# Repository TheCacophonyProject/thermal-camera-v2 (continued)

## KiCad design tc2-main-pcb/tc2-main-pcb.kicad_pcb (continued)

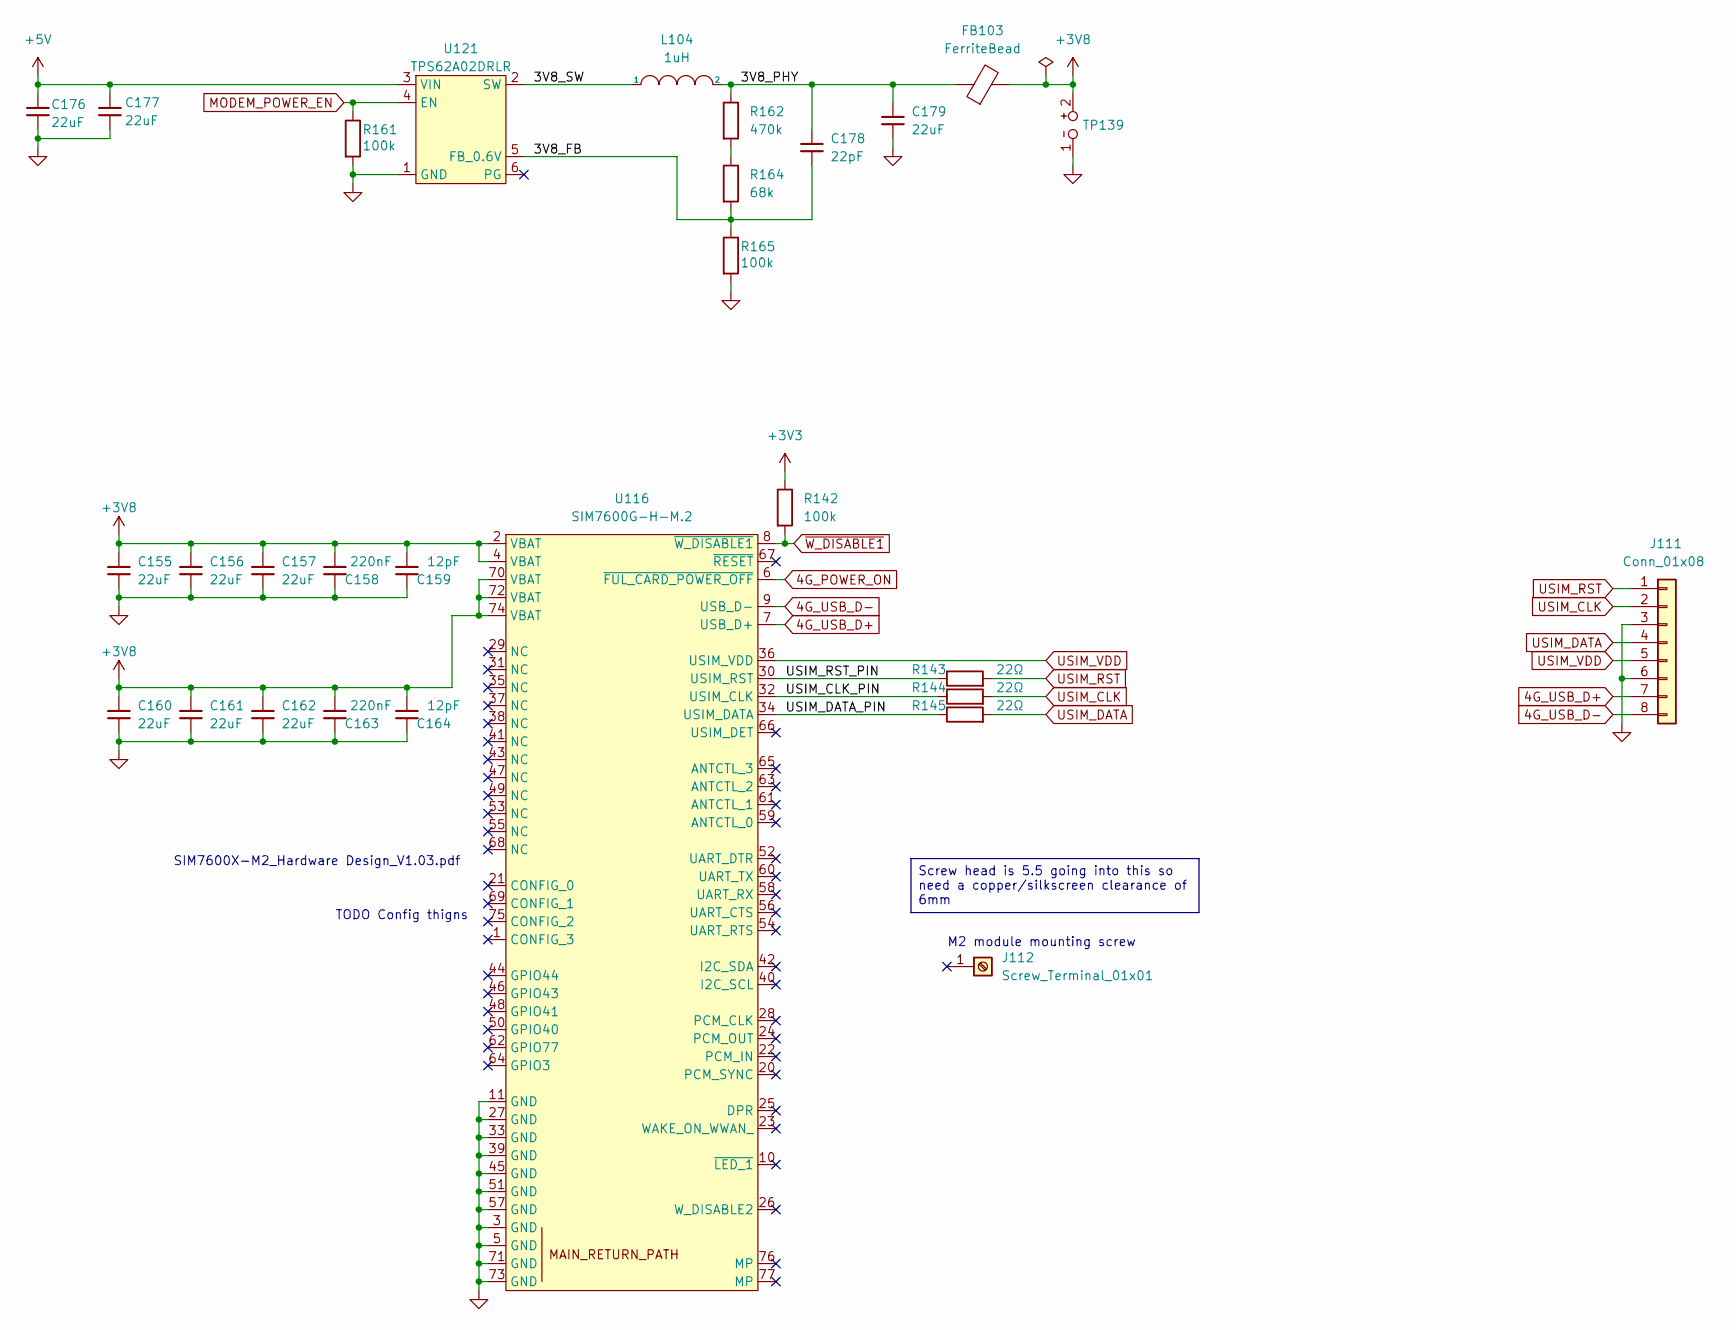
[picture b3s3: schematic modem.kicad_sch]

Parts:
C155, C156, C157, C160, C161, C162, C176, C177, C179: 22uF; C_0603_1608Metric; LCSC Part C86295
C158, C163: 220nF; C_0402_1005Metric; LCSC Part C16772
C159, C164: 12pF; C_0402_1005Metric; LCSC Part C1547
C178: 22pF; C_0402_1005Metric; LCSC Part C1555
FB103: FerriteBead; L_0805_2012Metric; LCSC Part C76818
J111: Conn_01x08; sim-usb-pcb
J112: Screw_Terminal_01x01; M2_modem_mount_screw; LCSC Part C2928176
L104: 1uH; L_1008_2520Metric; LCSC Part C285917
R142, R161, R165: 100k; R_0402_1005Metric; LCSC Part C25741
R143, R144, R145: 22Ω; R_0402_1005Metric; LCSC Part C25092
R162: 470k; R_0402_1005Metric; LCSC Part C319591
R164: 68k; R_0402_1005Metric; LCSC Part C445618
TP139: TP_2P; test-point-2p
U116: SIM7600G-H-M.2; M.2; LCSC Part C2761526
U121: TPS62A02DRLR; SOT-563; LCSC Part C5350187

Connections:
4G_POWER_ON: U116.6 (~FUL_CARD_POWER_OFF); also elsewhere on the board
4G_USB_D+: J111.7, U116.7 (USB_D+)
4G_USB_D-: J111.8, U116.9 (USB_D-)
+3V3: R142.1; also elsewhere on the board
+3V8: C155.1, C156.1, C157.1, C158.2, C159.2, C160.1, C161.1, C162.1, C163.2, C164.2, FB103.2, TP139.2, U116.2 (VBAT), U116.4 (VBAT), U116.70 (VBAT), U116.72 (VBAT), U116.74 (VBAT)
+5V: C176.1, C177.1, U121.3 (VIN); also elsewhere on the board
/modem/3V8_FB: C178.2, R164.2, R165.1, U121.5 (FB_0.6V)
/modem/3V8_PHY: C178.1, C179.1, FB103.1, L104.2, R162.1
/modem/3V8_SW: L104.1, U121.2 (SW)
/modem/USIM_CLK_PIN: R144.1, U116.32 (USIM_CLK)
/modem/USIM_DATA_PIN: R145.1, U116.34 (USIM_DATA)
/modem/USIM_RST_PIN: R143.1, U116.30 (USIM_RST)
GND: C155.2, C156.2, C157.2, C158.1, C159.1, C160.2, C161.2, C162.2, C163.1, C164.1, C176.2, C177.2, C179.2, J111.3, J111.6, R161.2, R165.2, TP139.1, U116.3 (GND), U116.5 (GND), U116.11 (GND), U116.27 (GND), U116.33 (GND), U116.39 (GND), U116.45 (GND), U116.51 (GND), U116.57 (GND), U116.71 (GND), U116.73 (GND), U121.1 (GND); also elsewhere on the board
MODEM_POWER_EN: R161.1, U121.4 (EN); also elsewhere on the board
unnamed: R162.2, R164.1
USIM_CLK: J111.2, R144.2
USIM_DATA: J111.4, R145.2
USIM_RST: J111.1, R143.2
USIM_VDD: J111.5, U116.36 (USIM_VDD)
~W_DISABLE1: R142.2, U116.8 (~W_DISABLE1); also elsewhere on the board

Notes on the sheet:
TODO Config thigns
M2 module mounting screw
SIM7600X-M2_Hardware Design_V1.03.pdf
Screw head is 5.5 going into this so need a copper/silkscreen clearance of 6mm

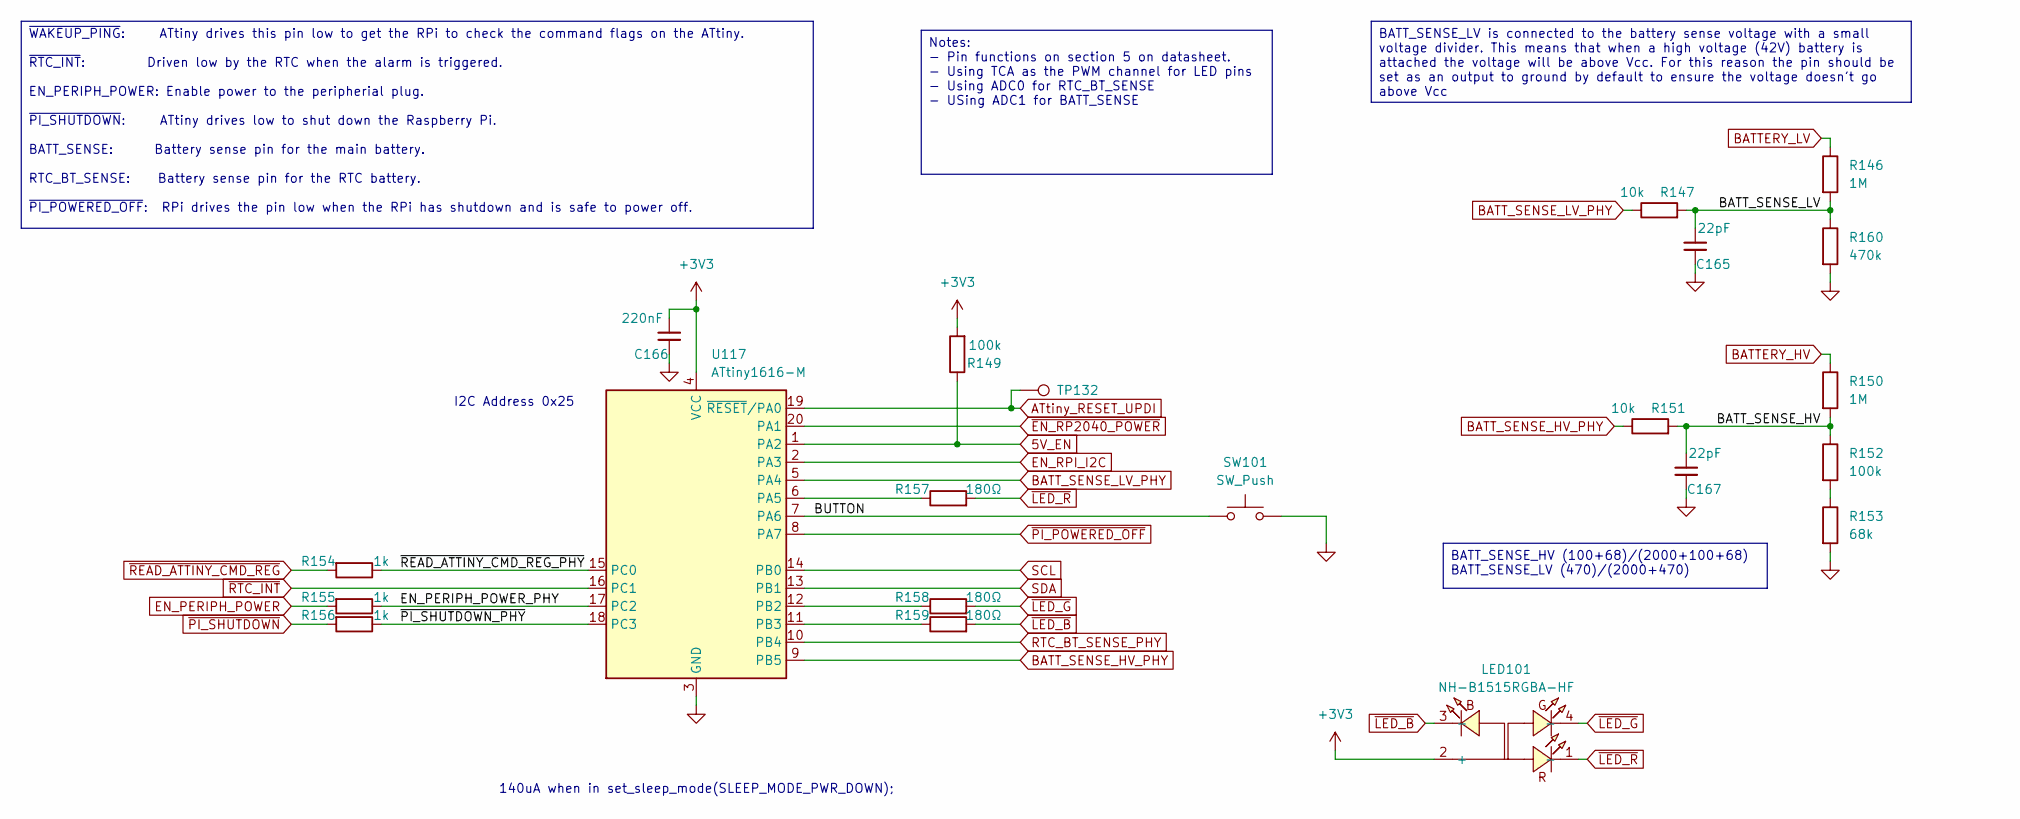
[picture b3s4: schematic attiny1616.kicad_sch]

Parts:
C165, C167: 22pF; C_0402_1005Metric; LCSC Part C1555
C166: 220nF; C_0402_1005Metric; LCSC Part C16772
LED101: NH-B1515RGBA-HF; LED-ARRAY-SMD_4P-L1.6-W1.5-TL_NH-B1515RGBA; LCSC Part C2874115
R146, R150: 1M; R_0603_1608Metric; LCSC Part C326730
R147, R151: 10k; R_0402_1005Metric; LCSC Part C25744
R149: 100k; R_0402_1005Metric; LCSC Part C25741
R152: 100k; R_0402_1005Metric; LCSC Part C445619
R153: 68k; R_0402_1005Metric; LCSC Part C445618
R154, R155, R156: 1k; R_0402_1005Metric; LCSC Part C11702
R157, R158, R159: 180Ω; R_0402_1005Metric; LCSC Part C38941
R160: 470k; R_0402_1005Metric; LCSC Part C319591
SW101: SW_Push; SW_PUSH_6mm; LCSC Part C4364951
TP132: TestPoint; TestPoint_Pad_D1.0mm
U117: ATtiny1616-M; VQFN-20-1EP_3x3mm_P0.4mm_EP1.7x1.7mm; LCSC Part C507118

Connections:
5V_EN: R149.1, U117.1 (PA2); also elsewhere on the board
+3V3: C166.2, LED101.2 (+), R149.2, U117.4 (VCC); also elsewhere on the board
/ATtiny1616/BATT_SENSE_HV: C167.2, R150.2, R151.2, R152.1
/ATtiny1616/BATT_SENSE_LV: C165.2, R146.2, R147.2, R160.1
/ATtiny1616/BUTTON: SW101.1, U117.7 (PA6)
/ATtiny1616/EN_PERIPH_POWER_PHY: R155.1, U117.17 (PC2)
/ATtiny1616/~PI_SHUTDOWN_PHY: R156.1, U117.18 (PC3)
/ATtiny1616/~READ_ATTINY_CMD_REG_PHY: R154.1, U117.15 (PC0)
ATtiny_RESET_UPDI: TP132.1 (1_1), U117.19 (~RESET/PA0); also elsewhere on the board
BATTERY_HV: R150.1; also elsewhere on the board
BATTERY_LV: R146.1; also elsewhere on the board
BATT_SENSE_HV_PHY: R151.1, U117.9 (PB5)
BATT_SENSE_LV_PHY: R147.1, U117.5 (PA4)
EN_PERIPH_POWER: R155.2; also elsewhere on the board
EN_RPI_I2C: U117.2 (PA3); also elsewhere on the board
GND: C165.1, C166.1, C167.1, R153.2, R160.2, SW101.2, U117.3 (GND), U117.21 (GND); also elsewhere on the board
unnamed: R152.2, R153.1
unnamed: R157.1, U117.6 (PA5)
unnamed: R158.1, U117.12 (PB2)
unnamed: R159.1, U117.11 (PB3)
RTC_BT_SENSE_PHY: U117.10 (PB4); also elsewhere on the board
SCL: U117.14 (PB0); also elsewhere on the board
SDA: U117.13 (PB1); also elsewhere on the board
~EN_RP2040_POWER: U117.20 (PA1); also elsewhere on the board
~LED_B: LED101.3 (-), R159.2
~LED_G: LED101.4 (-), R158.2
~LED_R: LED101.1 (-), R157.2
~PI_POWERED_OFF: U117.8 (PA7); also elsewhere on the board
~PI_SHUTDOWN: R156.2; also elsewhere on the board
~READ_ATTINY_CMD_REG: R154.2; also elsewhere on the board
~RTC_INT: U117.16 (PC1); also elsewhere on the board

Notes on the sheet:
140uA when in set_sleep_mode(SLEEP_MODE_PWR_DOWN);
I2C Address 0x25
BATT_SENSE_LV is connected to the battery sense voltage with a small voltage divider. This means that when a high voltage (42V) battery is attached the voltage will be above Vcc. For this reason the pin should be set as an output to ground by default to ensure the voltage doesn't go above Vcc
BATT_SENSE_HV (100+68)/(2000+100+68) BATT_SENSE_LV (470)/(2000+470)
~{WAKEUP_PING}: ATtiny drives this pin low to get the RPi to check the command flags on the ATtiny. ~{RTC_INT}: Driven low by the RTC when the alarm is triggered. EN_PERIPH_POWER: Enable power to the peripherial plug. ~{PI_SHUTDOWN}: ATtiny drives low to shut down the Raspberry Pi. BATT_SENSE: Batt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
Notes: - Pin functions on section 5 on datasheet. - Using TCA as the PWM channel for LED pins - Using ADC0 for RTC_BT_SENSE - USing ADC1 for BATT_SENSE

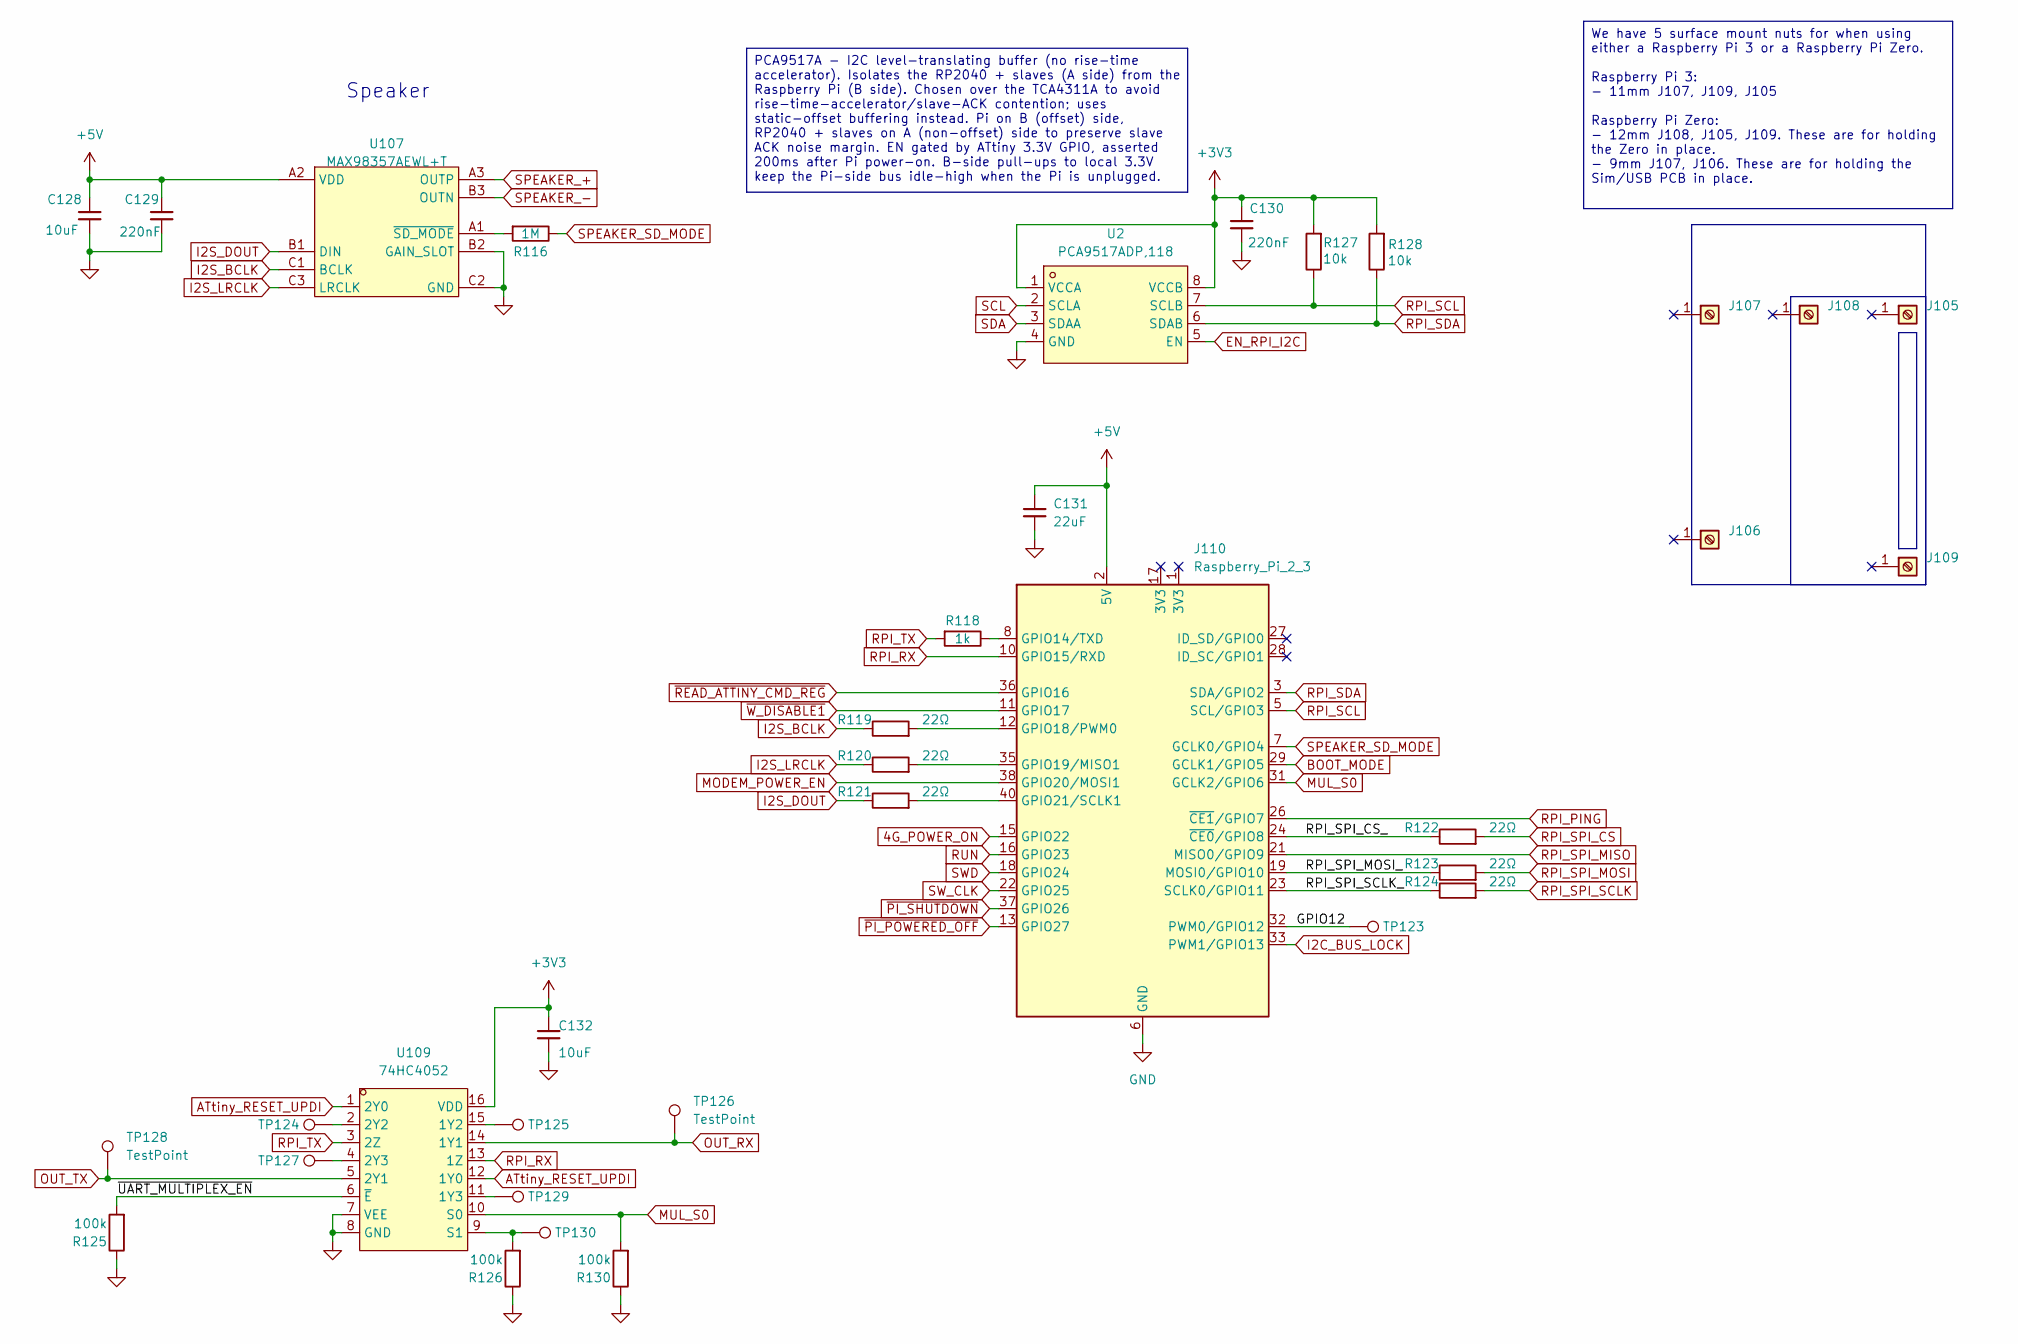
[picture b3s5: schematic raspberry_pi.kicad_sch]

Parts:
C128, C132: 10uF; C_0603_1608Metric; LCSC Part C19702
C129, C130: 220nF; C_0402_1005Metric; LCSC Part C16772
C131: 22uF; C_0603_1608Metric; LCSC Part C86295
J105, J106, J107, J108, J109: Screw_Terminal_01x01; smd_nut_SMTSO25; LCSC Part C2915630
J110: Raspberry_Pi_2_3; rpi-throughhole-socket; LCSC Part C350295
R116: 1M; R_0603_1608Metric; LCSC Part C326730
R118: 1k; R_0402_1005Metric; LCSC Part C11702
R119, R120, R121, R122, R123, R124: 22Ω; R_0402_1005Metric; LCSC Part C25092
R125, R126, R130: 100k; R_0402_1005Metric; LCSC Part C25741
R127, R128: 10k; R_0402_1005Metric; LCSC Part C25744
TP123, TP124, TP125, TP127, TP129, TP130: TestPoint; TP
TP126, TP128: TestPoint; TestPoint_Pad_D1.0mm
U2: PCA9517ADP,118; MSOP-8_3x3mm_P0.65mm; MPN PCA9517ADP,118; LCSC Part C80799
U107: MAX98357AEWL+T; WLP-9_L1.4-W1.3-P0.40-R3-C3-BR; JLC Part Extended Part
U109: 74HC4052; SOIC-16_3.9x9.9mm_P1.27mm; LCSC Part C11350

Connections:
4G_POWER_ON: J110.15 (GPIO22); also elsewhere on the board
+3V3: C130.2, C132.1, R127.2, R128.2, U2.1 (VCCA), U2.8 (VCCB), U109.16 (VDD); also elsewhere on the board
+5V: C128.1, C129.2, C131.1, J110.2 (5V), J110.4 (5V), U107.A2 (VDD); also elsewhere on the board
/Raspberry_Pi/GPIO12: J110.32 (PWM0/GPIO12), TP123.1 (1_1)
/Raspberry_Pi/RPI_SPI_CS_: J110.24 (~CE0/GPIO8), R122.1
/Raspberry_Pi/RPI_SPI_MOSI_: J110.19 (MOSI0/GPIO10), R123.1
/Raspberry_Pi/RPI_SPI_SCLK_: J110.23 (SCLK0/GPIO11), R124.1
/Raspberry_Pi/~UART_MULTIPLEX_EN: R125.2, U109.6 (~E)
ATtiny_RESET_UPDI: U109.1 (2Y0), U109.12 (1Y0); also elsewhere on the board
BOOT_MODE: J110.29 (GCLK1/GPIO5); also elsewhere on the board
EN_RPI_I2C: U2.5 (EN); also elsewhere on the board
GND: C128.2, C129.1, C130.1, C131.2, C132.2, J110.6 (GND), J110.9 (GND), J110.14 (GND), J110.20 (GND), J110.25 (GND), J110.30 (GND), J110.34 (GND), J110.39 (GND), R125.1, R126.1, R130.1, U2.4 (GND), U107.B2 (GAIN_SLOT), U107.C2 (GND), U109.7 (VEE), U109.8 (GND); also elsewhere on the board
I2C_BUS_LOCK: J110.33 (PWM1/GPIO13); also elsewhere on the board
I2S_BCLK: R119.1, U107.C1 (BCLK)
I2S_DOUT: R121.1, U107.B1 (DIN)
I2S_LRCLK: R120.1, U107.C3 (LRCLK)
MODEM_POWER_EN: J110.38 (GPIO20/MOSI1); also elsewhere on the board
MUL_S0: J110.31 (GCLK2/GPIO6), R130.2, U109.10 (S0)
unnamed: J110.8 (GPIO14/TXD), R118.1
unnamed: J110.12 (GPIO18/PWM0), R119.2
unnamed: J110.35 (GPIO19/MISO1), R120.2
unnamed: J110.40 (GPIO21/SCLK1), R121.2
unnamed: R116.2, U107.A1 (~SD_MODE)
unnamed: TP125.1 (1_1), U109.15 (1Y2)
unnamed: TP129.1 (1_1), U109.11 (1Y3)
unnamed: TP124.1 (1_1), U109.2 (2Y2)
unnamed: TP127.1 (1_1), U109.4 (2Y3)
unnamed: R126.2, TP130.1 (1_1), U109.9 (S1)
OUT_RX: TP126.1 (1_1), U109.14 (1Y1); also elsewhere on the board
OUT_TX: TP128.1 (1_1), U109.5 (2Y1); also elsewhere on the board
RPI_PING: J110.26 (~CE1/GPIO7); also elsewhere on the board
RPI_RX: J110.10 (GPIO15/RXD), U109.13 (1Z)
RPI_SCL: J110.5 (SCL/GPIO3), R127.1, U2.7 (SCLB)
RPI_SDA: J110.3 (SDA/GPIO2), R128.1, U2.6 (SDAB)
RPI_SPI_CS: R122.2; also elsewhere on the board
RPI_SPI_MISO: J110.21 (MISO0/GPIO9); also elsewhere on the board
RPI_SPI_MOSI: R123.2; also elsewhere on the board
RPI_SPI_SCLK: R124.2; also elsewhere on the board
RPI_TX: R118.2, U109.3 (2Z)
RUN: J110.16 (GPIO23); also elsewhere on the board
SCL: U2.2 (SCLA); also elsewhere on the board
SDA: U2.3 (SDAA); also elsewhere on the board
SPEAKER_+: U107.A3 (OUTP); also elsewhere on the board
SPEAKER_-: U107.B3 (OUTN); also elsewhere on the board
SPEAKER_SD_MODE: J110.7 (GCLK0/GPIO4), R116.1
SWD: J110.18 (GPIO24); also elsewhere on the board
SW_CLK: J110.22 (GPIO25); also elsewhere on the board
~PI_POWERED_OFF: J110.13 (GPIO27); also elsewhere on the board
~PI_SHUTDOWN: J110.37 (GPIO26); also elsewhere on the board
~READ_ATTINY_CMD_REG: J110.36 (GPIO16); also elsewhere on the board
~W_DISABLE1: J110.11 (GPIO17); also elsewhere on the board

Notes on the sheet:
Speaker
PCA9517A - I2C level-translating buffer (no rise-time accelerator). Isolates the RP2040 + slaves (A side) from the Raspberry Pi (B side). Chosen over the TCA4311A to avoid rise-time-accelerator/slave-ACK contention; uses static-offset buffering instead. Pi on B (offset) side, RP2040 + slaves on A (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
We have 5 surface mount nuts for when using either a Raspberry Pi 3 or a Raspberry Pi Zero. Raspberry Pi 3: - 11mm J107, J109, J105 Raspberry Pi Zero: - 12mm J108, J105, J109. These are for holding the Zero in place. - 9mm J107, J106. These are for holding the Sim/USB PCB in place.

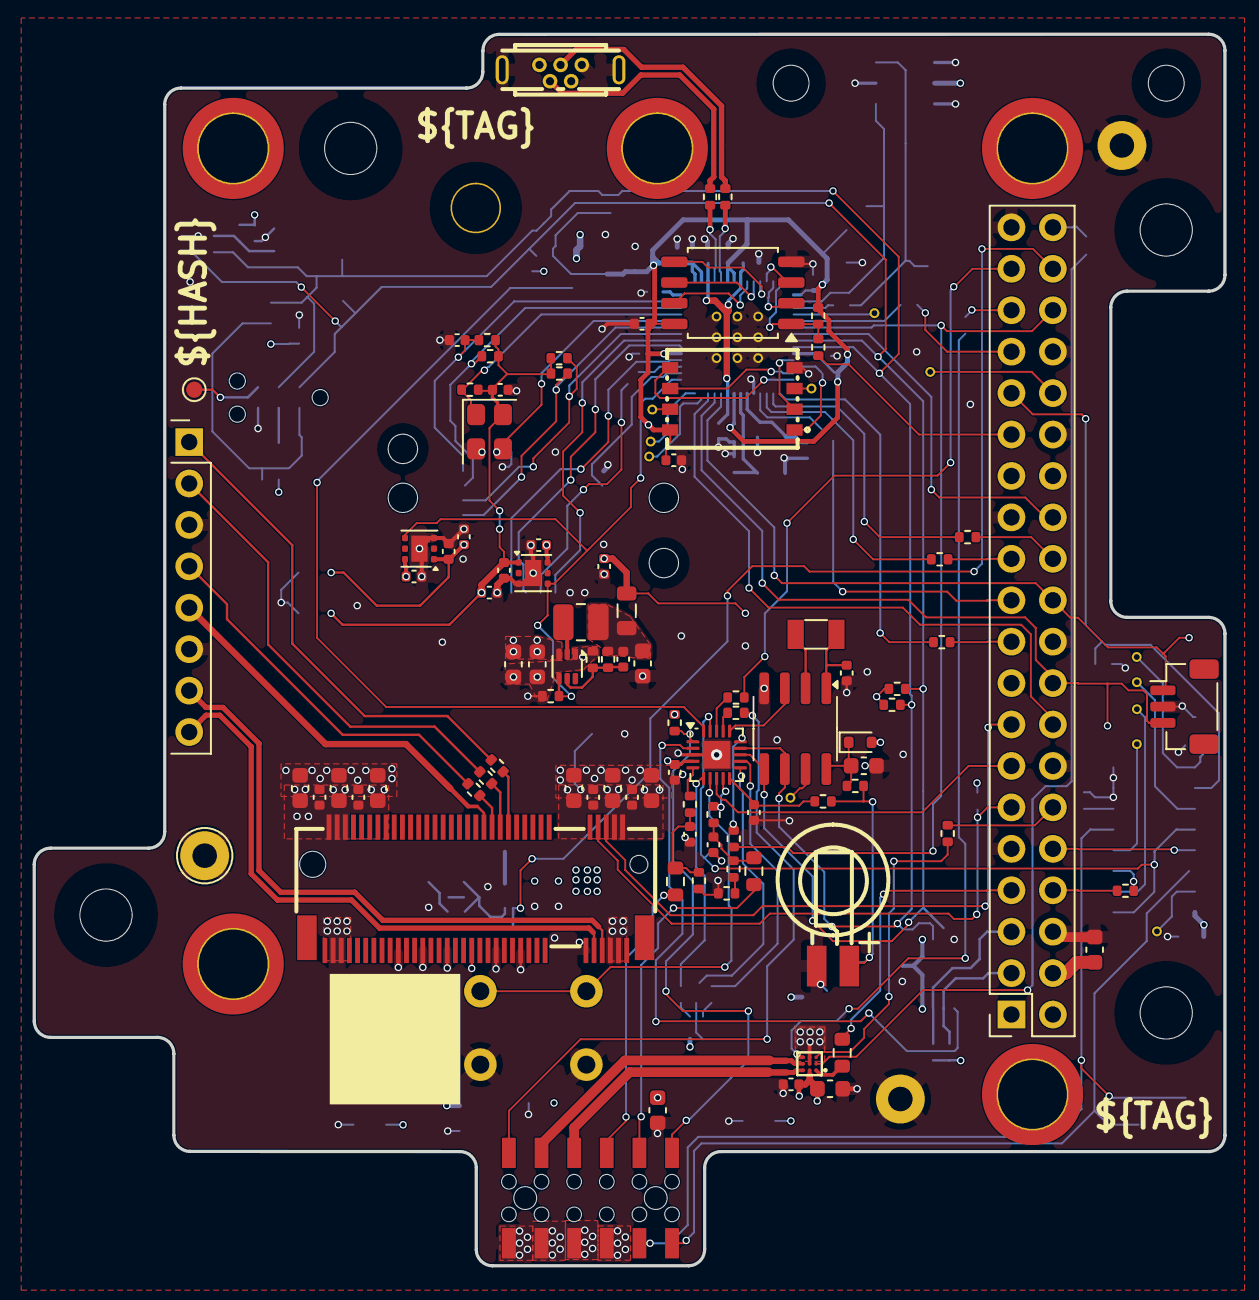
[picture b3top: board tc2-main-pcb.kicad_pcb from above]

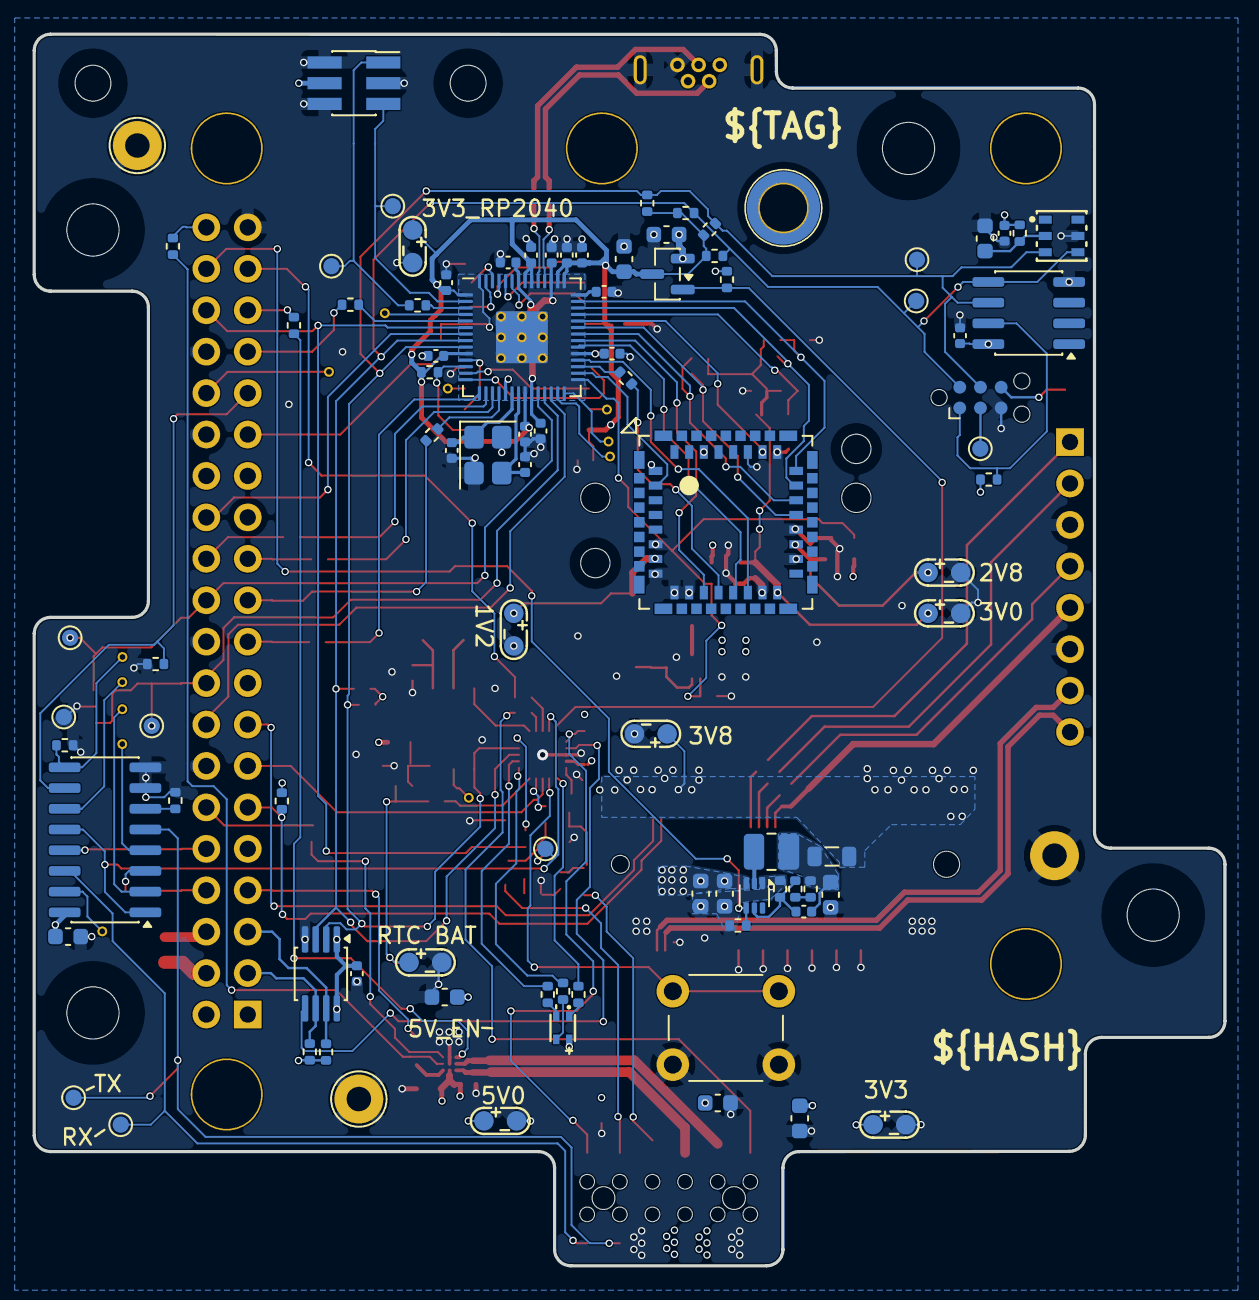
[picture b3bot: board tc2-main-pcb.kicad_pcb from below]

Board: 6 copper layers, 73.0 x 75.5 mm, 212 parts (108 on the bottom side), 143 nets.

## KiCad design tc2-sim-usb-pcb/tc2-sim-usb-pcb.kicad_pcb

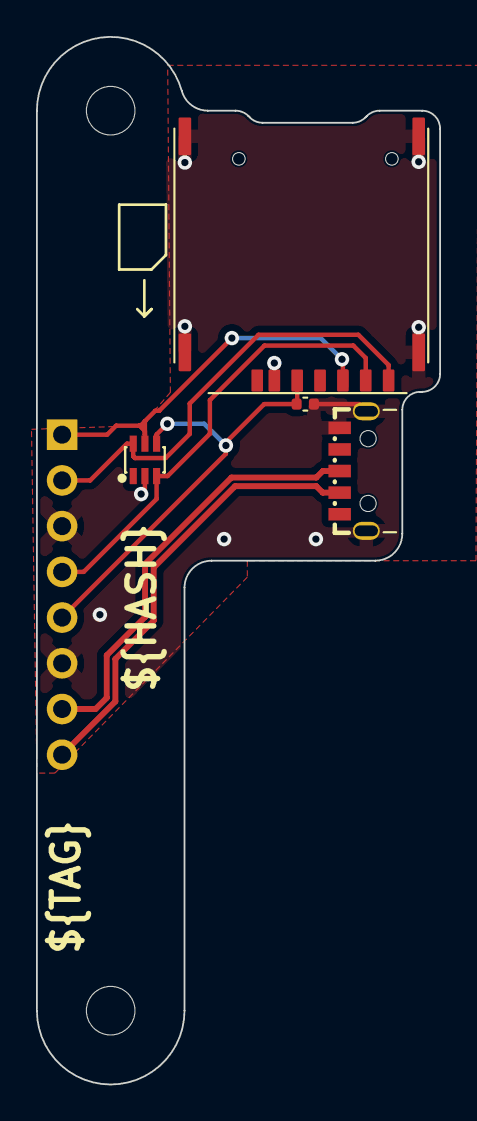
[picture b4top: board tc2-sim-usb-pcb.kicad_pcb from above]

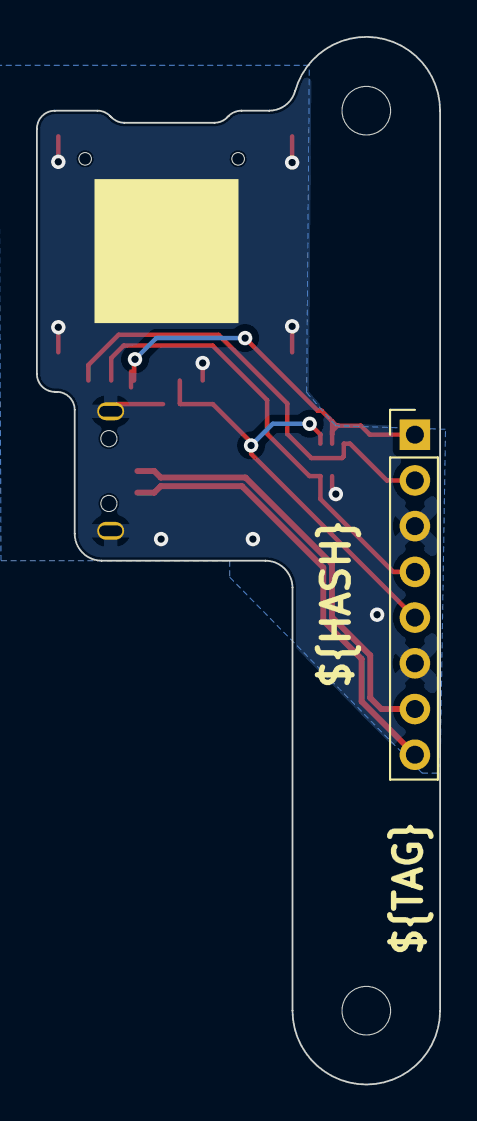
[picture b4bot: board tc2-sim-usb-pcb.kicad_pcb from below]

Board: 6 copper layers, 22.4 x 58.2 mm, 10 parts (2 on the bottom side), 7 nets.

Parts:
C501: 220nF; C_0402_1005Metric
D501: SMF05CT1G; SOT-363_L2.0-W1.3-P0.65-LS2.1-BR
H501, H502: MountingHole; MountingHole_2.7mm_M2.5
J501: Conn_01x08; Sim_connector
U501, U502: ziptie
U503: K-DYX-010
U504: JLCPCB_QR_8mm
USB501: U-G-M5WS-W-01; MICRO-USB-SMD_U-G-M5WS-W-01

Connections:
4G_USB_D+: J501.7, USB501.3 (D+)
4G_USB_D-: J501.8, USB501.2 (D-)
GND: C501.1, D501.2, J501.3, J501.6, U503.C5 (Gnd), U503.MP, U503.MP_2 (MP), U503.MP_3 (MP), U503.MP_4 (MP), USB501.5 (GND), USB501.6 (SHELL), USB501.7 (SHELL)
USIM_CLK: D501.6, J501.2, U503.C3 (CLK)
USIM_DATA: D501.3, J501.4, U503.C7 (I/O)
USIM_RST: D501.5, J501.1, U503.C2 (RST)
USIM_VDD: C501.2, D501.4, J501.5, U503.C1 (Vcc)

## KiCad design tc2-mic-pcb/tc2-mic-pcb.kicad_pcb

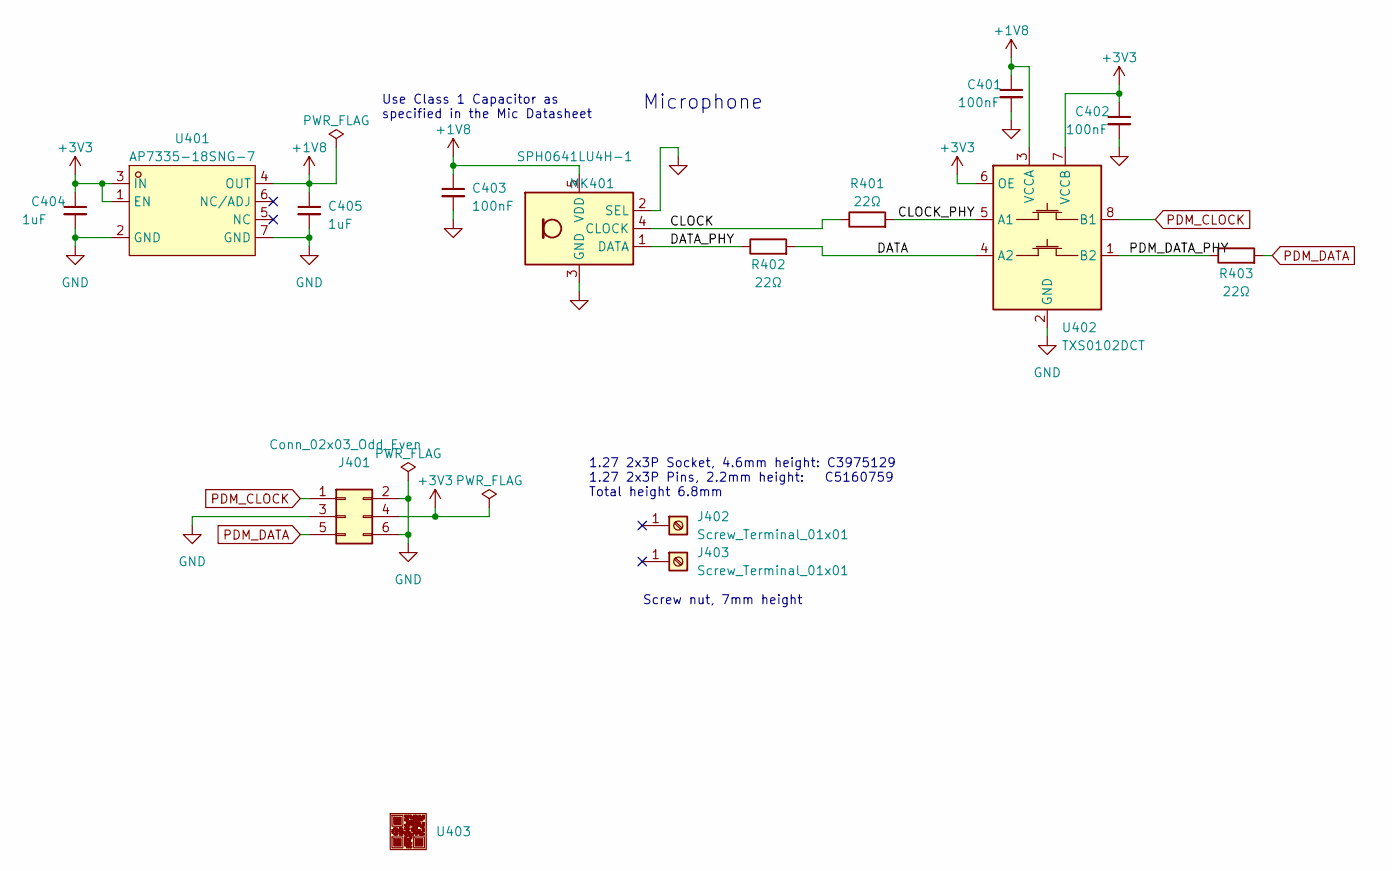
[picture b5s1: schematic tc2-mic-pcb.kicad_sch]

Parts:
C401, C402: 100nF; C_0402_1005Metric; LCSC Part C1525
C403: 100nF; C_1206_3216Metric; LCSC Part C170182
C404, C405: 1uF; C_0402_1005Metric; LCSC Part C52923
J401: Conn_02x03_Odd_Even; PinHeader_2x03_P1.27mm_Vertical_SMD; LCSC Part C5160759
J402, J403: Screw_Terminal_01x01; SMD_BD4.4-L4.4-D2.8; LCSC Part C2928186
MK401: SPH0641LU4H-1; Knowles_LGA-5_3.5x2.65mm_0.6mm_NPTH; LCSC Part C2879853
R401, R402, R403: 22Ω; R_0402_1005Metric; LCSC Part C25092
U401: AP7335-18SNG-7; U-DFN2020-6_L2.0-W2.0-P0.65-BL-EP; JLC Part Extended Part
U402: TXS0102DCT; SSOP-8_2.95x2.8mm_P0.65mm; LCSC Part C324082
U403: JLCPCB_QR_8mm

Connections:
+1V8: C401.1, C403.1, C405.1, MK401.5 (VDD), U401.4 (OUT), U402.3 (VCCA)
+3V3: C402.1, C404.1, J401.4, U401.1 (EN), U401.3 (IN), U402.6 (OE), U402.7 (VCCB)
/CLOCK: MK401.4 (CLOCK), R401.1
/CLOCK_PHY: R401.2, U402.5 (A1)
/DATA: R402.2, U402.4 (A2)
/DATA_PHY: MK401.1 (DATA), R402.1
/PDM_DATA_PHY: R403.1, U402.1 (B2)
GND: C401.2, C402.2, C403.2, C404.2, C405.2, J401.2, J401.3, J401.6, MK401.2 (SEL), MK401.3 (GND), U401.2 (GND), U401.7 (GND), U402.2 (GND)
PDM_CLOCK: J401.1, U402.8 (B1)
PDM_DATA: J401.5, R403.2

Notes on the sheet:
Use Class 1 Capacitor as specified in the Mic Datasheet
Microphone
Screw nut, 7mm height
1.27 2x3P Socket, 4.6mm height: C3975129 1.27 2x3P Pins, 2.2mm height: C5160759 Total height 6.8mm

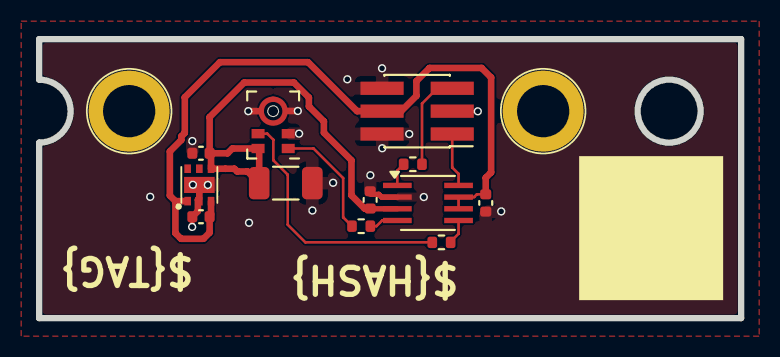
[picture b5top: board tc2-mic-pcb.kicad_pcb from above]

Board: 2 copper layers, 39.0 x 15.5 mm, 15 parts (0 on the bottom side), 10 nets.

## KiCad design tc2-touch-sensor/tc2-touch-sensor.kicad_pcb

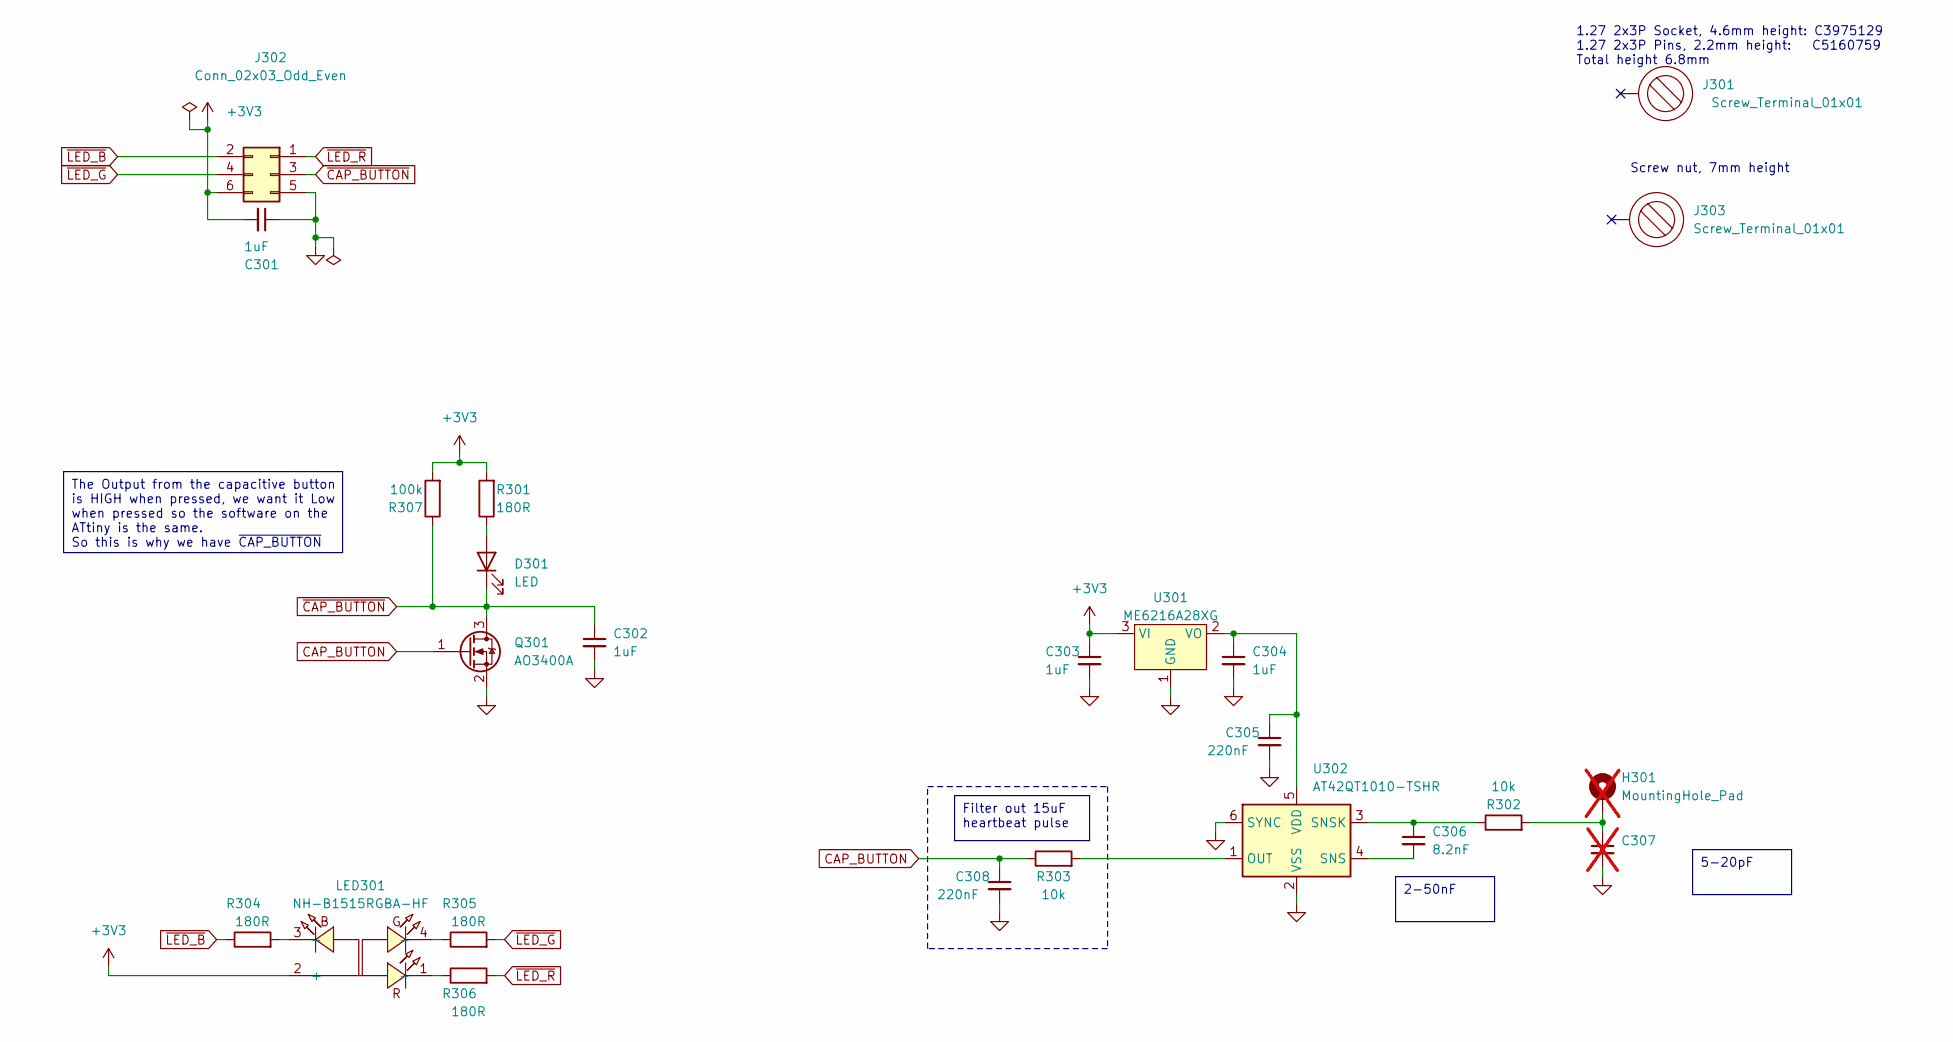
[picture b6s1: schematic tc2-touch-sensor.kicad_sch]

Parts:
C301, C302, C303, C304: 1uF; C_0402_1005Metric; LCSC C52923
C305, C308: 220nF; C_0402_1005Metric; LCSC C16772
C306: 8.2nF; C_0402_1005Metric; LCSC C309459
C307: C_0402_1005Metric; not fitted
D301: LED; QBLP655R-IW-2897; MPN QBLP655R-IW-2897; LCSC C6150270
H301: MountingHole_Pad; Touch_Pad; not fitted
J301, J303: Screw_Terminal_01x01; SMTWE2070MTJ; LCSC C2928186
J302: Conn_02x03_Odd_Even; PinHeader_2x03_P1.27mm_Vertical_SMD; LCSC C5160759
LED301: NH-B1515RGBA-HF; QBLP655R-RGB; JLC Part Extended Part
Q301: AO3400A; SOT-23; LCSC C20917
R301, R304, R305, R306: 180R; R_0402_1005Metric; LCSC C38941
R302, R303: 10k; R_0402_1005Metric; LCSC C25744
R307: 100k; R_0402_1005Metric; LCSC C25741
U301: ME6216A28XG; TSOT-23; LCSC C427601
U302: AT42QT1010-TSHR; SOT-23-6; LCSC C74512

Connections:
+3V3: C301.2, C303.1, J302.6, LED301.2 (+), R301.2, R307.2, U301.3 (VI)
CAP_BUTTON: C308.1, Q301.1 (G), R303.1
GND: C301.1, C302.2, C303.2, C304.2, C305.2, C307.2, C308.2, J302.5, Q301.2 (S), U301.1 (GND), U302.2 (VSS), U302.6 (SYNC)
unnamed: C307.1, H301.1, R302.2
unnamed: D301.2 (A), R301.1
unnamed: LED301.1 (-), R306.1
unnamed: LED301.3 (-), R304.2
unnamed: LED301.4 (-), R305.1
unnamed: C304.1, C305.1, U301.2 (VO), U302.5 (VDD)
unnamed: R303.2, U302.1 (OUT)
unnamed: C306.2, U302.4 (SNS)
unnamed: C306.1, R302.1, U302.3 (SNSK)
~CAP_BUTTON: C302.1, D301.1 (K), J302.3, Q301.3 (D), R307.1
~LED_B: J302.2, R304.1
~LED_G: J302.4, R305.2
~LED_R: J302.1, R306.2

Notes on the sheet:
5-20pF
Filter out 15uF heartbeat pulse
2-50nF
The Output from the capacitive button is HIGH when pressed, we want it Low when pressed so the software on the ATtiny is the same. So this is why we have ~{CAP_BUTTON}
1.27 2x3P Socket, 4.6mm height: C3975129 1.27 2x3P Pins, 2.2mm height: C5160759 Total height 6.8mm
Screw nut, 7mm height
